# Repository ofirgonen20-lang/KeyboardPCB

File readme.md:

# OFIR’s Hackpad – Custom 3×2 KMK Macropad with OLED, RGB & EC11 Encoder

A custom-designed 4×4 mechanical macropad built around the Seeed XIAO RP2040, featuring:

Matrix-scanned mechanical switches with diodes

SK6812 Mini RGB LEDs

0.91" OLED display

KMK firmware (CircuitPython)

# Project Images

  ## **schematic  1**

  ## **PCB layout**

  ## **case top & buttom**

  ## **assembled case**

# Bill of Materials (BOM)

1x XIAO RP2040

6x Cherry MX keyboard switch

1x EC11 rotary encoder with push switch

2x SK6812 MINI-E RGB LED

6x 1N4148 diode (DO-35)

1x 0.91" SSD1306 OLED (4-pin)

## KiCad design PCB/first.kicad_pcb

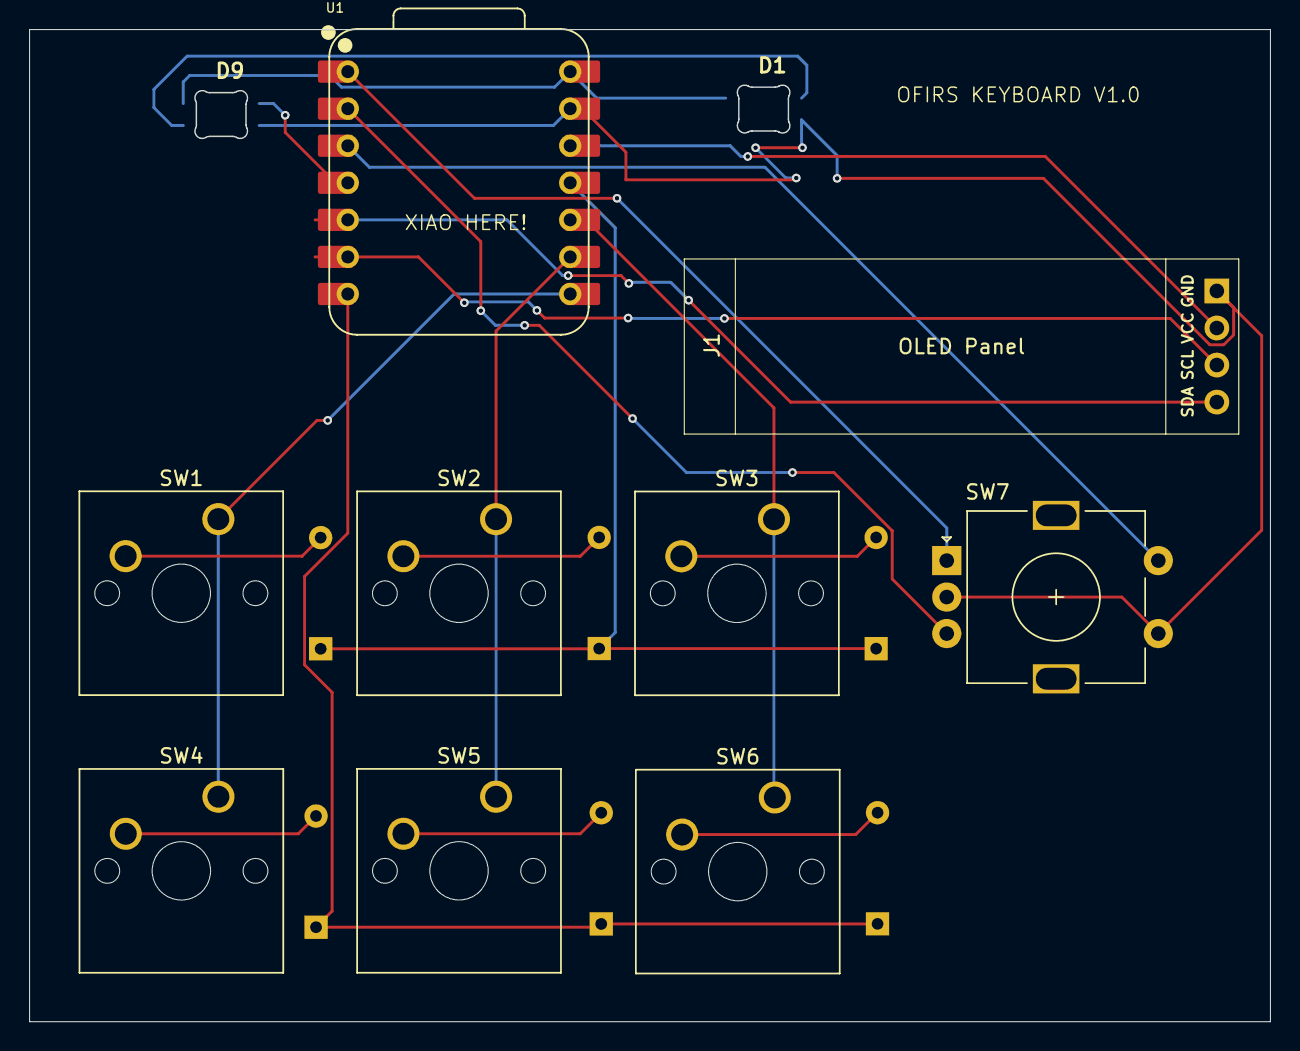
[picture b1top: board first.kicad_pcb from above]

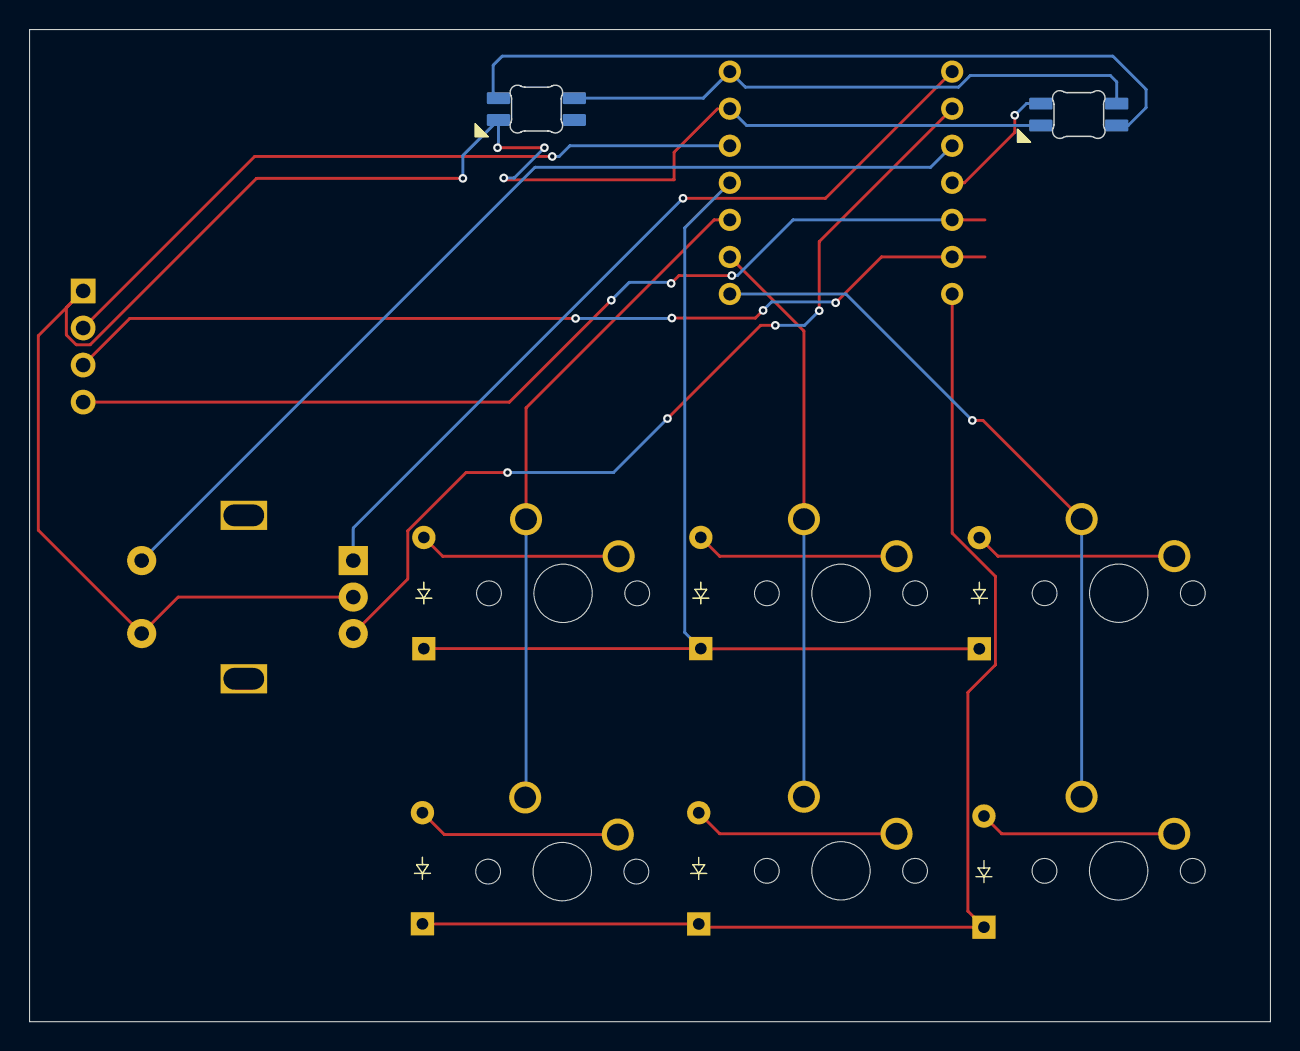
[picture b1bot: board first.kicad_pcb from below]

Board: 2 copper layers, 85.1 x 68.0 mm, 17 parts (6 on the bottom side), 21 nets.

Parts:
D1, D9: SK6812MINI-E; SK6812MINI-E_fixed
D3, D4, D5, D6, D7, D8: Diode_DO-35
J1: OLED1; SSD1306-0.91-OLED-4pin-128x32
SW1, SW2, SW3, SW4, SW5, SW6: SW_Push; SW_Cherry_MX_1.00u_PCB
SW7: RotaryEncoder_Switch; RotaryEncoder_Alps_EC11E-Switch_Vertical_H20mm
U1: XIAO-RP2040-DIP

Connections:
+5V: D1.1 (VDD), D9.1 (VDD), U1.14 (VBUS)
GND: D1.3 (VSS), D9.3 (VSS), J1.1, SW7.C, SW7.S1, U1.13 (GND)
unnamed: D1.4 (DIN), D9.2 (DOUT)
unnamed: D3.2 (A), SW1.2
unnamed: D4.2 (A), SW2.2
unnamed: D5.2 (A), SW3.2
unnamed: D6.2 (A), SW4.2
unnamed: D7.2 (A), SW5.2
unnamed: D8.2 (A), SW6.2
unnamed: D9.4 (DIN), U1.4 (GPIO29/ADC3/A3)
unnamed: J1.2, U1.12 (3V3)
unnamed: J1.3, U1.6 (GPIO7/SCL)
unnamed: J1.4, U1.5 (GPIO6/SDA)
unnamed: SW7.A, U1.1 (GPIO26/ADC0/A0)
unnamed: SW7.B, U1.2 (GPIO27/ADC1/A1)
unnamed: SW7.S2, U1.3 (GPIO28/ADC2/A2)
column 0: SW1.1, SW4.1, U1.8 (GPIO1/RX)
column 1: SW2.1, SW5.1, U1.9 (GPIO2/SCK)
column 2: SW3.1, SW6.1, U1.10 (GPIO4/MISO)
row 0: D3.1 (K), D4.1 (K), D5.1 (K), U1.11 (GPIO3/MOSI)
row 1: D6.1 (K), D7.1 (K), D8.1 (K), U1.7 (GPIO0/TX)

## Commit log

2026-01-16 New repository for my keyboard project!
2026-01-16 extractig files out of folder
2026-01-16 adding a readme
2026-01-16 Add project details and images to readme.txt
2026-01-16 test
2026-01-16 undo changes
2026-01-16 chagne to readme.md
2026-01-16 Revert "undo changes"
    This reverts commit 57722fd6a8be7ce412332d8cc41ec4601ecc6a61.
2026-01-16 Revert "chagne to readme.md"
    This reverts commit 7fa04ec192b1d9ebf08340a656307d74b0c26738.
2026-01-16 Remove PCB image from readme
    Removed PCB image from the readme.
2026-01-17 removing case.png
2026-01-17 updating readme
2026-01-17 adding a BOM
